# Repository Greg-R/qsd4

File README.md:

# QSD4

This is the PCB for the QSD4 receiver module for the T41 "Software Defined Transceiver".
The PCB was designed using the open-source design tool Kicad 7.

The QSD4 evolved from the original V010 design which remains the most recently published
receiver module for the T41 Software Defined Transceiver.

The goals of the QSD4 are to improve receiver performance, and in particular, the performance
in the 10 meter amateur radio band.  Please note that the designer of this project does not
own a laboratory full of expensive test equipment.  Much of the verification of the receiver
performance has been done "on the air".  There are no guarantees or other warranties of the
performance of this receiver module.  What you see is what you get!

Gerber files for PCB fabrication are included in the gerbers folder.
A PDF of the schematic (qsd4.pdf) is included for quick viewing of the circuit design.

Please note that the components used in this design increase the cost compared to the
original design.  However, the board is easier to build.  A link to a public Digikey
BOM is included so that the prospective builder can evaluate the cost before proceeding.

## Divide-by-2 versus Divide-by-4

The original QSD uses a divide-by-4 quadrature LO generator circuit.  This is a robust
circuit which produces high-quality quadrature local oscillator waveforms.  However,
the circuit has a trade-off and that is the requirement for VHF range frequencies in the
higher amateur HF bands.

For example, reception of a SSB signal at 28.510 MHz requires a frequency of:

(28.510 MHz + 48 kHz) * 4 = 114.232 MHz

Note the 48 kHz term which is the IF frequency.

This frequency is applied to the quadrature generator which is composed of a dual flip-flop
integrated circuit.  The circuit is powered from the 3.3 volt supply.

The flip-flop device is a type 74AC74.  The specification sheet is here:

<https://www.ti.com/lit/ds/symlink/sn74ac74.pdf>

The specification of interest, fclock with Vcc = 3.3 volts, is on page 4, and the maximum is 95 MHz.
This is insufficient to support the 10 Meter band.

One page the same specification is shown for Vcc = 5.0 volts, and the maximum increases to 125 MHz.
This shows a method to increase the frequency range, however, a matching 5.0 volt specified multiplexer
must be used.  A 5.0 volt multiplexer is in fact available at no cost penalty.

For optimal quadrature circuit performance, the coaxial cable between the Main board and the QSD4 should be
as short as possible.

## A Summary of Methods to Extend the T41 Frequency Range

The T41 is an "Experimenter's Platform", and there is no right or wrong way to solve a problem.
It is the experiment; the journey of discovery and amateur radio fun and adventure is the destination!

Here are a few ways to experiment with T41 frequency range expansion:

1.  Change the bias voltage on the 74AC74 from 3.3 volts to 5.0 volts.  Change the multiplexer IC to a part
specified for 5.0 volt operation.  This changes increases the frequency response of the flip-flop device.
2.  Change the 74AC74 to a device specified for higher frequencies while leaving the bias at 3.3 volts.  The
device is the 74LVC74.  The specification sheet is here:  <https://assets.nexperia.com/documents/data-sheet/74LVC74A.pdf>.
3.  Change the divide-by-4 circuit to the divide-by-2 circuit as described above.  This circuit is slightly more complex,
however, it has large margin to the upper frequency limits of the components at 10 meters.  6 meter operation may be possible.
There is no known low-frequency limit to the divide-by-2 (or divide-by-4) circuit.
4.  The T41 V012 design generates quadrature using an internal phase-shift circuit, such that one clock output is in-phase
and another clock output is shifted by 90 degrees.  This is directly applied to the multiplexing (demodulator) device,
and thus this circuit is very simple.  This also exploits the maximum upper frequency range of the Si5351 phase-lock-loop IC.  
On the other hand, this introduces a low frequency limit and it may not be possible to cover the LF and VLF amateur bands with this scheme.

The QSD4 circuit uses either method #1 or method #2.  Method #1 is what I have used during prototyping of the QSD4.
A zero ohm jumper selects either 3.3 or 5.0 volts applied to the quadrature generator circuit.

## Other Changes to the QSD4 Circuit Design

The QSD4 receiver module circuitry is almost entirely revised compared to its ancestor the V010 QSD.

### RF Amplifier

The discrete bipolar transistor RF amplifier is replaced with a Mini-Circuits integrated wideband amplifier:

<https://www.minicircuits.com/pdfs/GALI-39+.pdf>

Using this device is easy as it requires only a bias resistor and two coupling capacitors.  There is a series
of similar devices in the same package.  This particular device may not have the optimal gain and intermodulation
performance, however, it will be easy to substitute and experiment with other Mini-Circuits amplifiers in the same
family.

### Pi RF Attenuator

The problem with many of the integrated RF amplifiers is that they have too much gain!  Too much gain will reduce
the intermodulation and general strong-signal handling of the receiver.  Too much gain will have negligible impact
on receiver sensitivity.

A Pi resistive attenuator is added between the output of the RF amplifier and the input of the demodulator.
Thus the front-end gain can be adjusted to optimize both receiver sensitivity and intermodulation performance.

### Double-Balanced Quadrature Sampling Demodulator

The original V010 demodulator circuit is a single-balanced design.  The QSD4 is upgraded to double-balanced.
This requires an input transformer with a tapped secondary:

<https://www.minicircuits.com/pdfs/ADT4-6T+.pdf>

The tapped secondary provides the means of applying a common-mode bias to the demodulator device.
Using this ready-made transformer means no toroid winding!  However, it is expensive:  US$6.25.

### Balanced Output Summing Capacitors

The output of the demodulator uses "differential mode" integration capacitors.  The idea here is to balance
the output circuit to the highest degree possible.  The capacitors should be specified to 1% tolerance.  The typical
shunt capacitors are also provided.  The capacitor values in this circuit may be further optimized.

### Instrumentation Amplifiers

"Instrumentation amplifiers" replace the op-amps from the V010 circuit.  The instrumentation amplifiers are intended
to improve the symmetry and balance of the demodulator circuit, thus improving performance, and in particular the image rejection.

Another benefit of the instrumentation amplifiers is the simplification of the circuit.  A single resistor sets the gain.
The gain setting resistors should be specified to 1% tolerance.

A disadvantage of the instrumentation amplifiers is higher cost.  The AD8226 device cost is US$3.77.  Quantity 2 are required.

### Power Supply Decoupling

The power supplies routed through the 16 wire ribbon cable are prone to noise, most likely from the Main board.
Extra decoupling components were added to clean up the power supplies.  This has been noted in a lower noise floor
of the displayed spectrum.

### Option for 3.3 or 5.0 Volts Biasing and Comments on Reference Regulators

A zero ohm jumper is placed to select either 3.3 or 5.0 volt supply bias to the quadrature and demodulator devices.
It is also necessary to change the instrumentation amplifier reference regulators depending on the the chosen bias voltage.
Use 1.8 volt regulators with 3.3 volt bias, or a 2.5 volt regulator with 5.0 volt bias.

There are independent regulators U7 and U8 for the instrumentation amplifiers.  It may be possible to use a single regulator
for both.  A jumper resistor R16 can be placed to implement this change.  The capacitor C26 and U8 are not used.  This
change has not been tested yet, however, there is a good probability it will work fine.

### Connectors

The I/Q output connector is changed to surface mount.  The RF SMA connectors are the same, or they can be changed to right-angle
connectors to improve coaxial cable routing.  The 16 pin IDC connector is the same as the V010 board.

### PCB Layout

The PCB layout was completed using Kicad version 7.  This is an open-source tool, unlike the "Dip Trace" commercial product used
to design the V010 and also the V012 boards.

The layout in the quadrature generator and demodulator areas was very carefully routed for maximum frequency performance.
The QSD4 is approximately the same board size as V010, but there is enough area to add additional circuitry if desired.

The prototype PCBs were fabricated by PCBWay at a cost of US$1.00 each.  Shipping was about US$25.00 for quantity 5 boards.

## Bill Of Material (BOM)

A public Digikey BOM is here:

<https://www.digikey.com/en/mylists/list/WJHL6RPJHR>

This BOM includes parts to build a board with 5.0 volt biasing.  This is assumed to be the highest performance configuration.

Please note that specific parts may or may not be available when attempting to order.  It is the responsibility of the builder
to find subsitutes as required.

## Build Tips

In general, QSD4 is easier to build than the original V010/V011 series boards.  There are a few items to be aware of to avoid
build errors.

The most probable error(s) are incorrect orientation of the flip-flop, multiplexer, transformer, and instrumentation amplifier devices.  The integrated circuits have round dots located near pin 1.  The transformer has a visible center tap, and this should be connected to the output side of the circuit.

There are also 3 leaded electrolytic capacitors.  The markings for these parts are clear on the PCB.

Here are details on each part with regards to proper orientation of the board.  The descriptions are viewing the top side of the board, with the "T41 EXPERIMENTERS PLATFORM" near the bottom of the board in normal left-to-right reading orientation.

### Transformer TR1

The transformer TR1 should be placed with the "dot" at the upper right corner.  The textual markings will be upside down.

### 74AC74 Dual Flip-Flop U4

Pin 1 should be in the upper left corner.  This is marked with a small white dot on the PCB.
Note that both the flip-flop and the multiplexer are 4.4 mm TSOP type packages.

### 3253 Multiplexer U3

Pin 1 is at the upper left.  So the part is placed with the dot up, towards the flip-flop device.
So for the QSD4, the flip-flop and the multiplexer pin 1 dots should both be upper left.

### Instrumentation Amplifiers AD8226 U5 and U6

Only U5 has the Pin 1 indicated with a dot on the PCB.  However, both parts are oriented the same, with Pin 1 towards the upper left.  There is a dot on the parts to indicate Pin 1, however, it is very hard to see.  The package is beveled on the Pin 1 side; this is easy to see.

### Non-placed Parts

C20 and C21 are not used.

R29 and R30 are zero-ohm jumpers.  Place R29 for 5.0 volt bias on the quadrature generator.  This is the recommended configuration, and don't place R30 which is the 3.3 volt jumper.

### Bottom Side Parts

There is 1 capacitor on the bottom side.  This should be soldered last.  I was able to use a hot air gun without any problems with the top-side components desoldering.

R16 is placed on the bottom side in the case of using only one of the reference voltage regulators.

### SMA Connectors

Take a good look at the placement of the board in your T41 radio.  You will want the SMA connectors of the QSD2 in the orientation for easy coaxial cable routing.  I used 90 degree connectors as this was the easiest for extensive testing, but not necessarily the best for permanent installation.  Also, you may choose to put the SMAs on one side or the other for optimal cable routing.

Please note that the cable from the Main board to J1, which is the receive local oscillator, should be as short as possible.

### High Resolution Photos of QSD4

Links to photos of a fully constructed QSD4 follow.

<https://drive.google.com/file/d/1aspcZNfzApl-qxwgoq-D433Be0dcwM16/view?usp=sharing>

<https://drive.google.com/file/d/1kP5jGNJovGSlniU-m27XpsKZK9AjJI5x/view?usp=sharing>

<https://drive.google.com/file/d/10uLrnD7fPuJHRcCnD-vJwYjdFCpwKCTR/view?usp=sharing>

<https://drive.google.com/file/d/1hoJ_x_dKpq-bHXMOEn-O8QFBmkSheuwZ/view?usp=sharing>

Please note that the above photos show a version 1.0 board.  The Gerber files are for
a revised version 1.1.  The only significant difference is the placement of a 0 ohm resistor
on the back side to allow optional sharing of a single 2.5 volt reference source.

## References and Further Reading

The QSD4 is an attempt to integrate the best circuits from several sources into a high-performance HF receiver module.
Here is a list of sources which inspired the design of the QSD4:

1.  "Digital Signal Processing and Software Defined Radio, Theory and Construction of the T41-EP Software Defined Transceiver",
by Albert F. Peter, AC8GY, and Dr. Jack Purdum, W8TEE.  This is the ultimate resource for builders of the T41 Software Defined
Transceiver:  <https://www.amazon.com/Software-Defined-Radio-Transceiver-Construction/dp/B09WYP1ST8>
2.  "A Software Defined Radio for the Masses, Part 4" by Gerald Youngblood, AC5OG.  This shows the circuit for the double-balanced
demodulator circuit and the use of instrumentation amplifiers on the output circuit.
<https://www.arrl.org/files/file/Technology/tis/info/pdf/030304qex020.pdf>
3.  The Rod Gatehouse 2022 transceiver website:  https://ad5gh.wordpress.com/2022-sdr-transceiver/
Rod took the original T41 SDT design and evolved it into a high-performance digital mode radio.  Excellent circuit upgrades!
4.  "The Lentz Receiver: Tayloe Evolved" by H. Scott Lentz, AG7FF.  An interesting discussion of several design features of the
"Lentz Receiver" which improve the performance of the typical "Tayloe Detector" style HF receiver.
<https://www.arrl.org/files/file/QEX_Next_Issue/2023/05%20may-jun%202023/05%202023%20TofC.pdf>
5.  The QSD2 which is very similar to the QSD4:
<https://github.com/Greg-R/qsd2>

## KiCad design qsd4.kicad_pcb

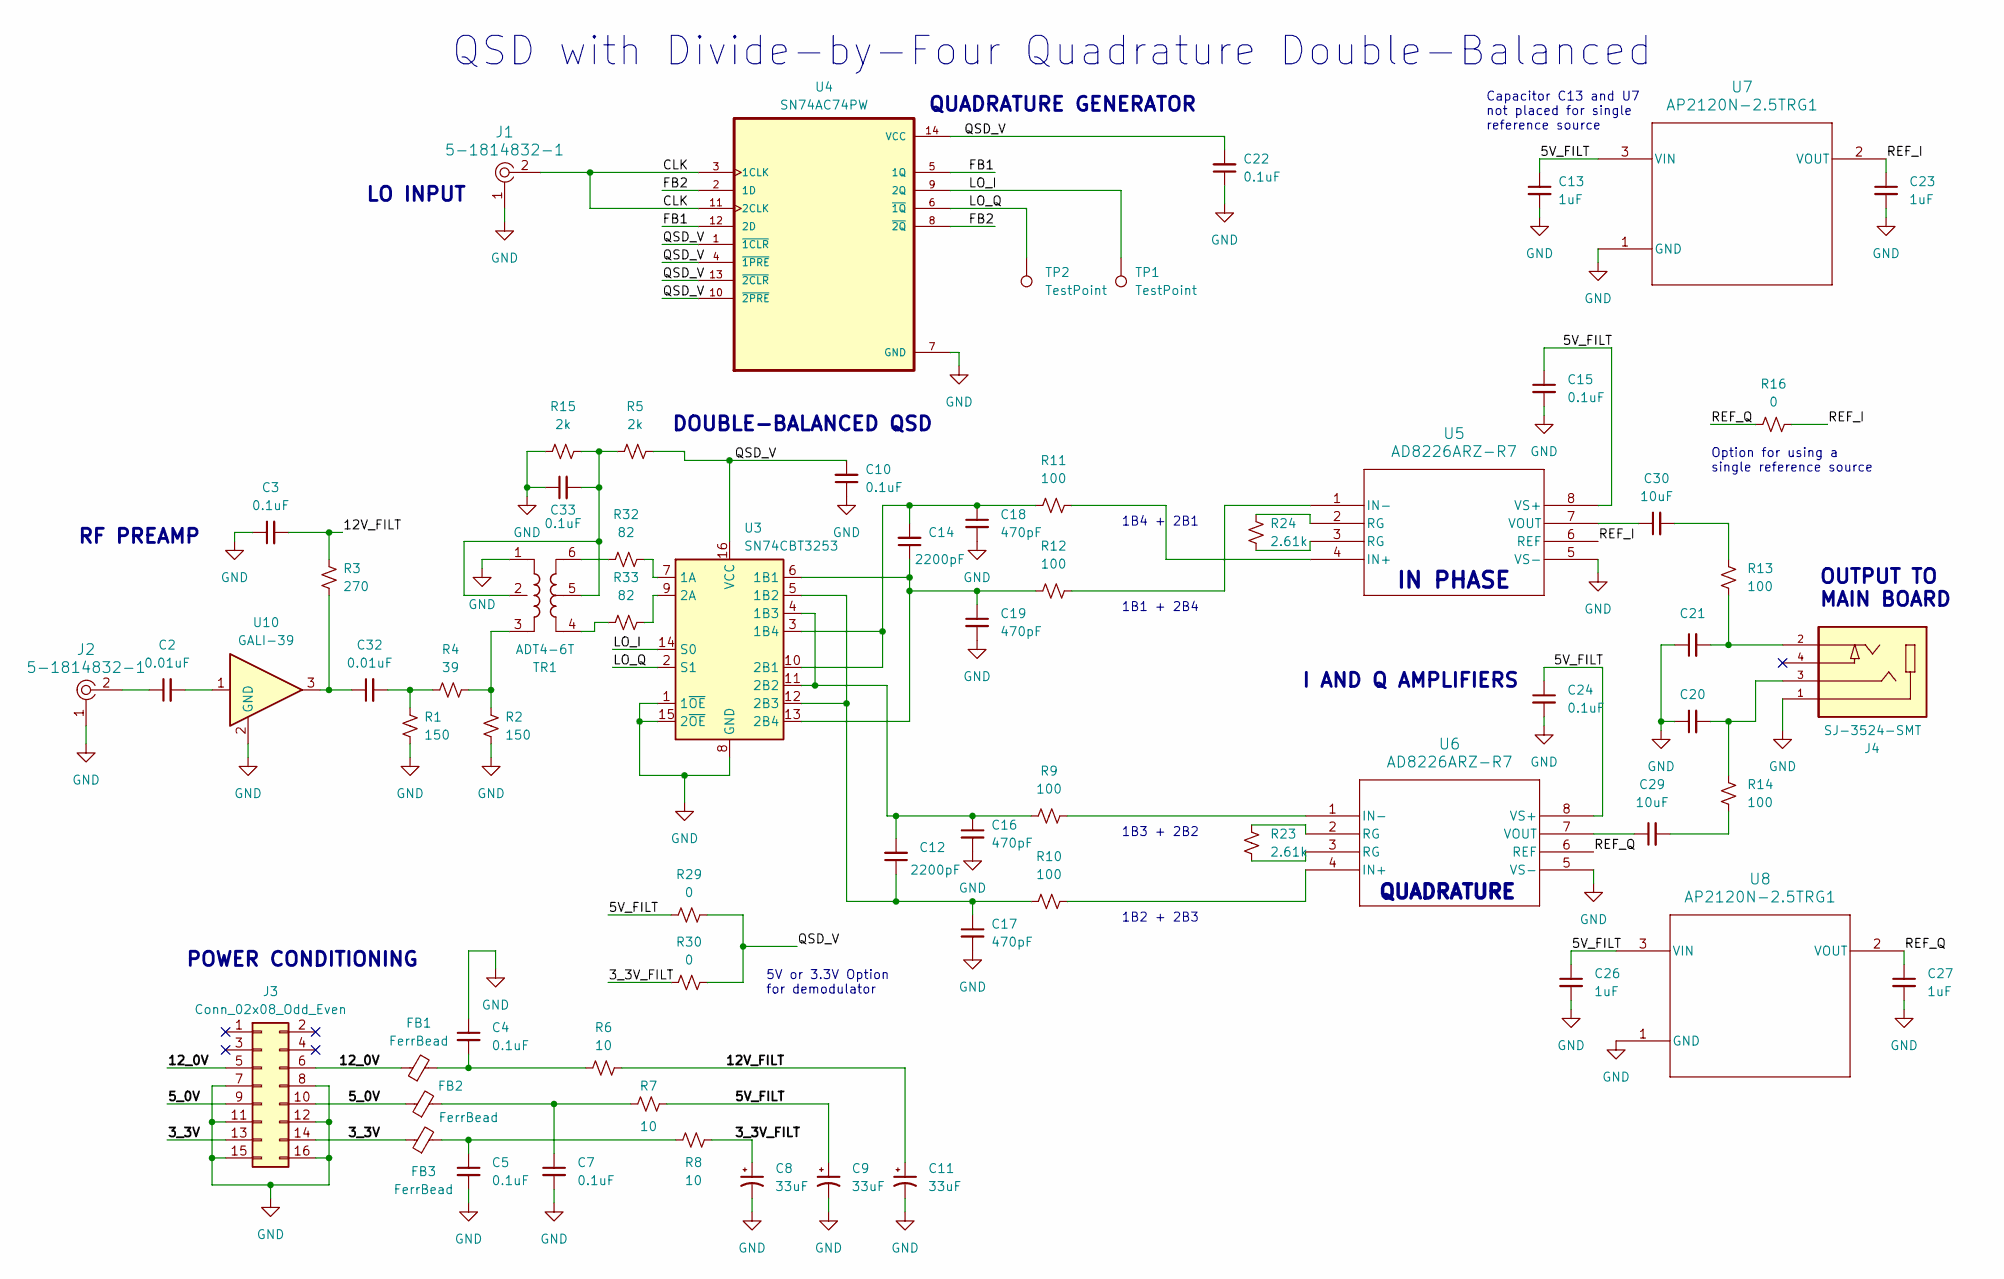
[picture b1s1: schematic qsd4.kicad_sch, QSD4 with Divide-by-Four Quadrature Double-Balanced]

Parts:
C2, C32: 0.01uF; C_1206_3216Metric
C3, C4, C5, C7, C10, C15, C22, C24, C33: 0.1uF; C_1206_3216Metric
C8, C9, C11: 33uF; CP_Radial_D5.0mm_P2.00mm
C12, C14: 2200pF; C_1206_3216Metric
C13, C23, C26, C27: 1uF; C_1206_3216Metric
C16, C17, C18, C19: 470pF; C_1206_3216Metric
C20, C21: C_1206_3216Metric
C29, C30: 10uF; C_1206_3216Metric
FB1, FB2, FB3: FerrBead; L_1206_3216Metric
J1, J2: 5-1814832-1; RF_SMA_Vertical_5-1814832-1; MPN 5-1814832-1; Digi-Key_PN A97594-ND
J3: Conn_02x08_Odd_Even; IDC-Header_2x08_P2.54mm_Vertical
J4: SJ-3524-SMT; CUI_SJ-3524-SMT; PARTREV 1.03
R1, R2: 150; R_1206_3216Metric
R3: 270; R_1206_3216Metric
R4: 39; R_1206_3216Metric
R5, R15: 2k; R_1206_3216Metric
R6, R7, R8: 10; R_1206_3216Metric
R9, R10, R11, R12, R13, R14: 100; R_1206_3216Metric
R16, R29, R30: 0; R_1206_3216Metric
R23, R24: 2.61k; R_1206_3216Metric
R32, R33: 82; R_1206_3216Metric
TP1, TP2: TestPoint; TestPoint_Pad_D1.0mm
TR1: ADT4-6T; Mini-Circuits_CD637_H5.23mm
U3: SN74CBT3253; TSSOP-16_4.4x5mm_P0.65mm
U4: SN74AC74PW; TSSOP-14_4.4x5mm_P0.65mm
U5, U6: AD8226ARZ-R7; R_8_ADI
U7, U8: AP2120N-2.5TRG1; SOT-23_DIO
U10: GALI-39; SOT-89-3

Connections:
/3_3V: FB3.1, J3.13, J3.14
/3_3V_FILT: C8.1, R8.2, R30.1
/5V_FILT: C9.1, C13.1, C15.1, C24.1, C26.1, R7.2, R29.1, U5.8 (VS+), U6.8 (VS+), U7.3 (VIN), U8.3 (VIN)
/5_0V: FB2.1, J3.9, J3.10
/12V_FILT: C3.2, C11.1, R3.1, R6.2
/12_0V: FB1.1, J3.5, J3.6
/CLK: J1.2, U4.3 (1CLK), U4.11 (2CLK)
/FB1: U4.5 (1Q), U4.12 (2D)
/FB2: U4.2 (1D), U4.8 (~2Q)
/LO_I: TP1.1, U3.14 (S0), U4.9 (2Q)
/LO_Q: TP2.1, U3.2 (S1), U4.6 (~1Q)
/QSD_V: C10.2, C22.2, R5.2, R29.2, R30.2, U3.16 (VCC), U4.1 (~1CLR), U4.4 (~1PRE), U4.10 (~2PRE), U4.13 (~2CLR), U4.14 (VCC)
/REF_I: C23.1, R16.2, U5.6 (REF), U7.2 (VOUT)
/REF_Q: C27.1, R16.1, U6.6 (REF), U8.2 (VOUT)
GND: C3.1, C4.1, C5.2, C7.2, C8.2, C9.2, C10.1, C11.2, C13.2, C15.2, C16.2, C17.2, C18.2, C19.2, C20.1, C21.1, C22.1, C23.2, C24.2, C26.2, C27.2, C33.1, J1.1, J2.1, J3.7, J3.8, J3.11, J3.12, J3.15, J3.16, J4.1, R1.2, R2.2, R15.1, TR1.1, U3.1 (1~OE), U3.8 (GND), U3.15 (2~OE), U4.7 (GND), U5.5 (VS-), U6.5 (VS-), U7.1 (GND), U8.1 (GND), U10.2 (GND)
unnamed: C2.1, J2.2
unnamed: C2.2, U10.1
unnamed: C4.2, FB1.2, R6.1
unnamed: C5.1, FB3.2, R8.1
unnamed: C7.1, FB2.2, R7.1
unnamed: C20.2, J4.3, R14.2
unnamed: C21.2, J4.2, R13.1
unnamed: C29.2, R14.1
unnamed: C30.2, R13.2
unnamed: C32.1, R3.2, U10.3
unnamed: C32.2, R1.1, R4.1
unnamed: R2.1, R4.2, TR1.3
unnamed: R23.1, U6.3 (RG)
unnamed: R23.2, U6.2 (RG)
unnamed: R24.1, U5.2 (RG)
unnamed: R24.2, U5.3 (RG)
unnamed: R32.1, TR1.6
unnamed: R33.1, TR1.4
unnamed: C33.2, R5.1, R15.2, TR1.2 (NOCONN), TR1.5
unnamed: R32.2, U3.7 (1A)
unnamed: C14.1, C19.1, R12.1, U3.6 (1B1), U3.13 (2B4)
unnamed: C12.1, C17.1, R10.1, U3.5 (1B2), U3.12 (2B3)
unnamed: C12.2, C16.1, R9.1, U3.4 (1B3), U3.11 (2B2)
unnamed: C14.2, C18.1, R11.1, U3.3 (1B4), U3.10 (2B1)
unnamed: R33.2, U3.9 (2A)
unnamed: R11.2, U5.4 (IN+)
unnamed: R12.2, U5.1 (IN-)
unnamed: C30.1, U5.7 (VOUT)
unnamed: R10.2, U6.4 (IN+)
unnamed: R9.2, U6.1 (IN-)
unnamed: C29.1, U6.7 (VOUT)

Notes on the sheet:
1B2 + 2B3
1B3 + 2B2
QUADRATURE
LO INPUT
IN PHASE
DOUBLE-BALANCED QSD
QUADRATURE GENERATOR
Option for using a single reference source
POWER CONDITIONING
RF PREAMP
1B4 + 2B1
OUTPUT TO MAIN BOARD
5V or 3.3V Option for demodulator
I AND Q AMPLIFIERS
1B1 + 2B4
Capacitor C13 and U7 not placed for single reference source
QSD with Divide-by-Four Quadrature Double-Balanced

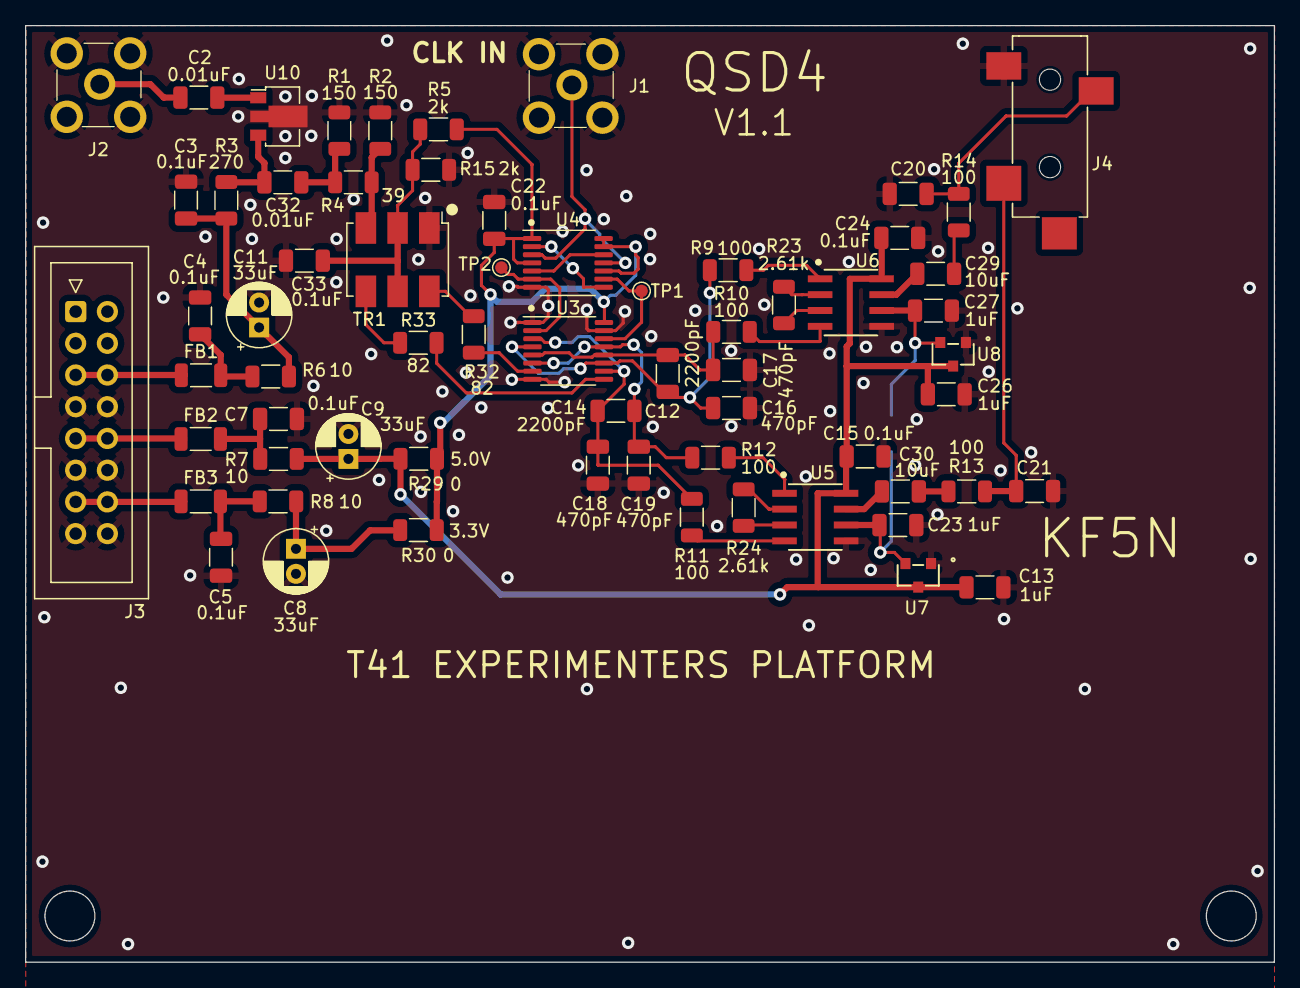
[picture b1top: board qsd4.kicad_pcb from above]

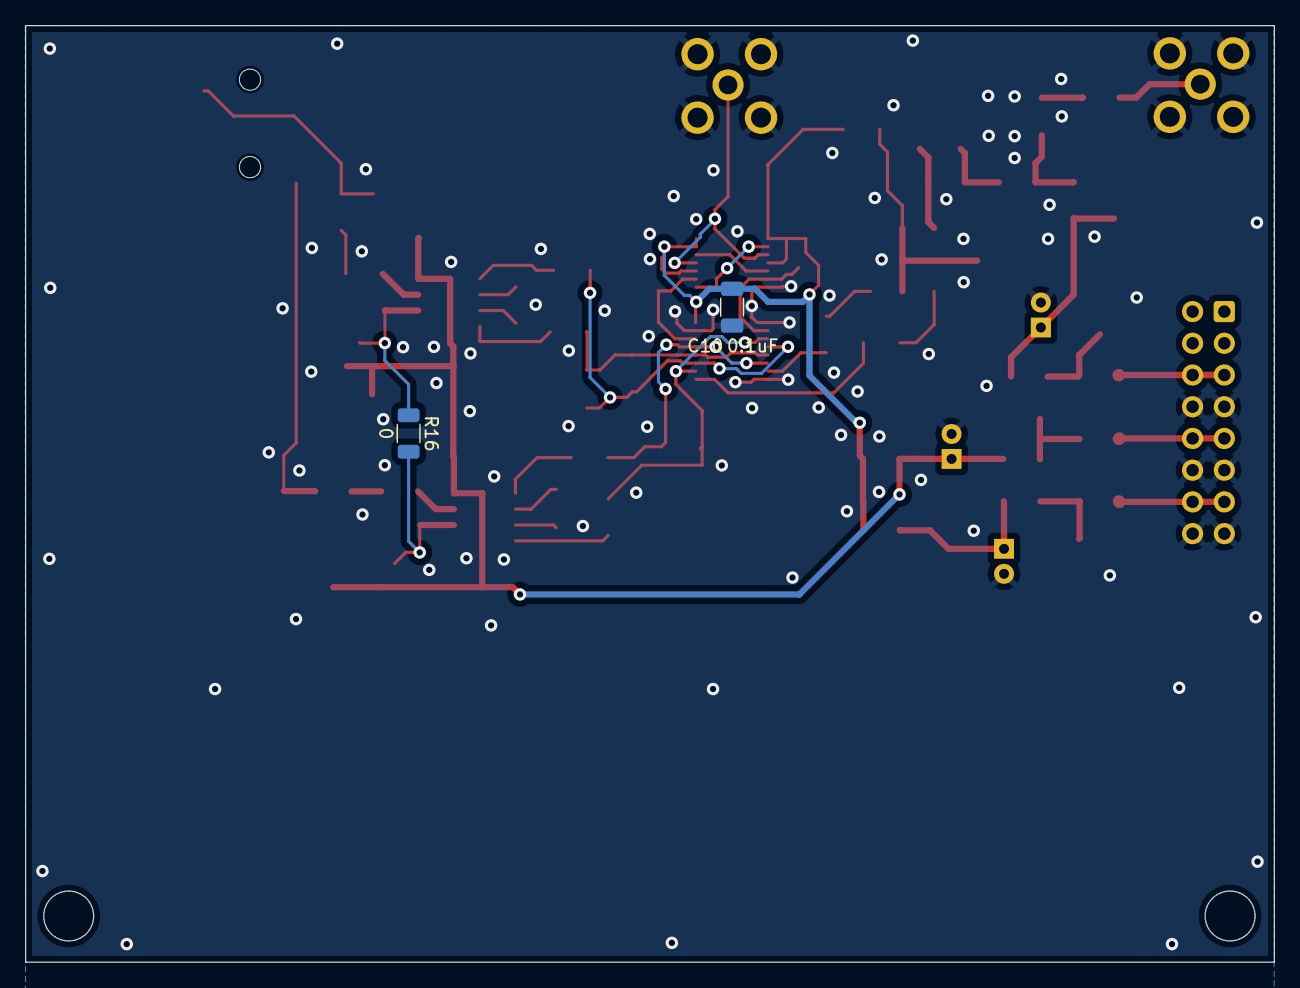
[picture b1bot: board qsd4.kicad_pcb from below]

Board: 2 copper layers, 100.0 x 75.0 mm, 67 parts (2 on the bottom side), 46 nets.

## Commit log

2023-10-30 Initial commit.
2023-11-17 Push to github.
2023-11-17 Removed gerber zip file and spec sheets.
2023-11-17 Removing backups from repository.
2023-11-17 Added .gitignore.
2023-11-18 Version 1.1 PCB for the QSD4. Documentation updated.
2023-11-18 Minor update to README.md.
